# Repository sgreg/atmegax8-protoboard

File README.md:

# ATmega8X Protoboard
### No fuzz ISP connector board for ATmega48/88/168/328 DIP28

One of those nights where I started something fresh with an ATmega controller and had to detach my breadboard ISP connector adapter from another ongoig project, and I started to wish I wouldn't have to. Breadboards are messy enough without trying to fiddle out single wires. Plus it's some poorly soldered DIY adapter that might just lose a wire any day.

Some time later that night the ATmega8X Protoboard was designed and sent to OSH Park.

Really, nothing fancy, just a little PCB with place for a DIP28 ATmega, an ISP connector and a decoupling capacitor with connectors for a breadboard, i.e. the most basic components for *any* project.

The ISP connector is meant for ATmega48/88/168/328 series microcontrollers, I actually have not checked if others use the same pinout for ISP. If so, it's gonna work with those as well. **Use at your own risk.**

Repository contains KiCad schematics, PCB layout and Gerber files.
Once I received the PCBs and verified they work and fit to the breadboard, it'll be shared on OSH Park.

## Revision B

Resized PCB and added a jumper to optionally route AVCC to VCC.

It was nice to have each pin number added to the PCB in revision A, but the PCB ended up simply too large this way. Placed on a bradboard, it occupied three rows on each side, leaving onl two rows left for wires for each pin. To make matters worse, the additional PCB margin made only one single row really usable.

Revision B squeezes it all more tight together and minimizes the PCB margin. The silk screen pin numbering had to be removed for this though.

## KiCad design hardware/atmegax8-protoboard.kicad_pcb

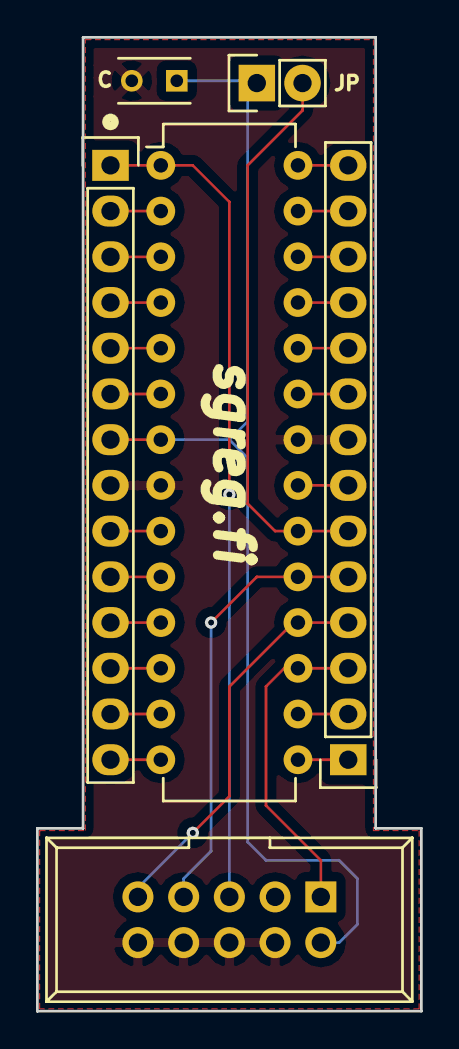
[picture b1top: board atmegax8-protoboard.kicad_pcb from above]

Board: 2 copper layers, 21.3 x 54.1 mm, 6 parts (0 on the bottom side), 27 nets.

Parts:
C1: 100n; C_Rect_L4_W2.5_P2.5
IC1: ATMEGA328-P; DIP-28_W7.62mm
JP1: JUMPER; Socket_Strip_Straight_1x02
P1: CONN1; Socket_Strip_Straight_1x14
P2: CONN2; Socket_Strip_Straight_1x14
P3: SERPROG; IDC_Header_Straight_10pins

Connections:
/AREF: IC1.21, P2.7
/AVCC: IC1.20, JP1.2, P2.6
/GND: C1.2, IC1.8, IC1.22, P1.8, P2.8, P3.4, P3.6, P3.8, P3.10
/PB0: IC1.14, P1.14
/PB1: IC1.15, P2.1
/PB2: IC1.16, P2.2
/PB3: IC1.17, P2.3, P3.1
/PB4: IC1.18, P2.4, P3.9
/PB5: IC1.19, P2.5, P3.7
/PB6: IC1.9, P1.9
/PB7: IC1.10, P1.10
/PC0: IC1.23, P2.9
/PC1: IC1.24, P2.10
/PC2: IC1.25, P2.11
/PC3: IC1.26, P2.12
/PC4: IC1.27, P2.13
/PC5: IC1.28, P2.14
/PD0: IC1.2, P1.2
/PD1: IC1.3, P1.3
/PD2: IC1.4, P1.4
/PD3: IC1.5, P1.5
/PD4: IC1.6, P1.6
/PD5: IC1.11, P1.11
/PD6: IC1.12, P1.12
/PD7: IC1.13, P1.13
/RESET: IC1.1, P1.1, P3.5
/VCC: C1.1, IC1.7, JP1.1, P1.7, P3.2

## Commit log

2016-03-08 Revision A schematic and PCB layout
2016-03-08 Added _autosave*kicad_pcb to gitignore
2016-05-05 Rev. B schematic, added jumper to route AVCC to VCC
2016-05-05 Rev B. PCB, minimized size, re-routed and added jumper
2016-05-05 Added Revision B information
2016-05-05 Rev. B Gerber files
2016-05-05 Fixed AVCC track separating GND fill zone
2016-05-29 Eh, typo fix..

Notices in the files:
hardware/atmegax8-protoboard.kicad_pcb:
Licensed under CERN OHDL v.1.2
